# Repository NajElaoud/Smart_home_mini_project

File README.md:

# Smart_home_mini_project
Mini projet educatif

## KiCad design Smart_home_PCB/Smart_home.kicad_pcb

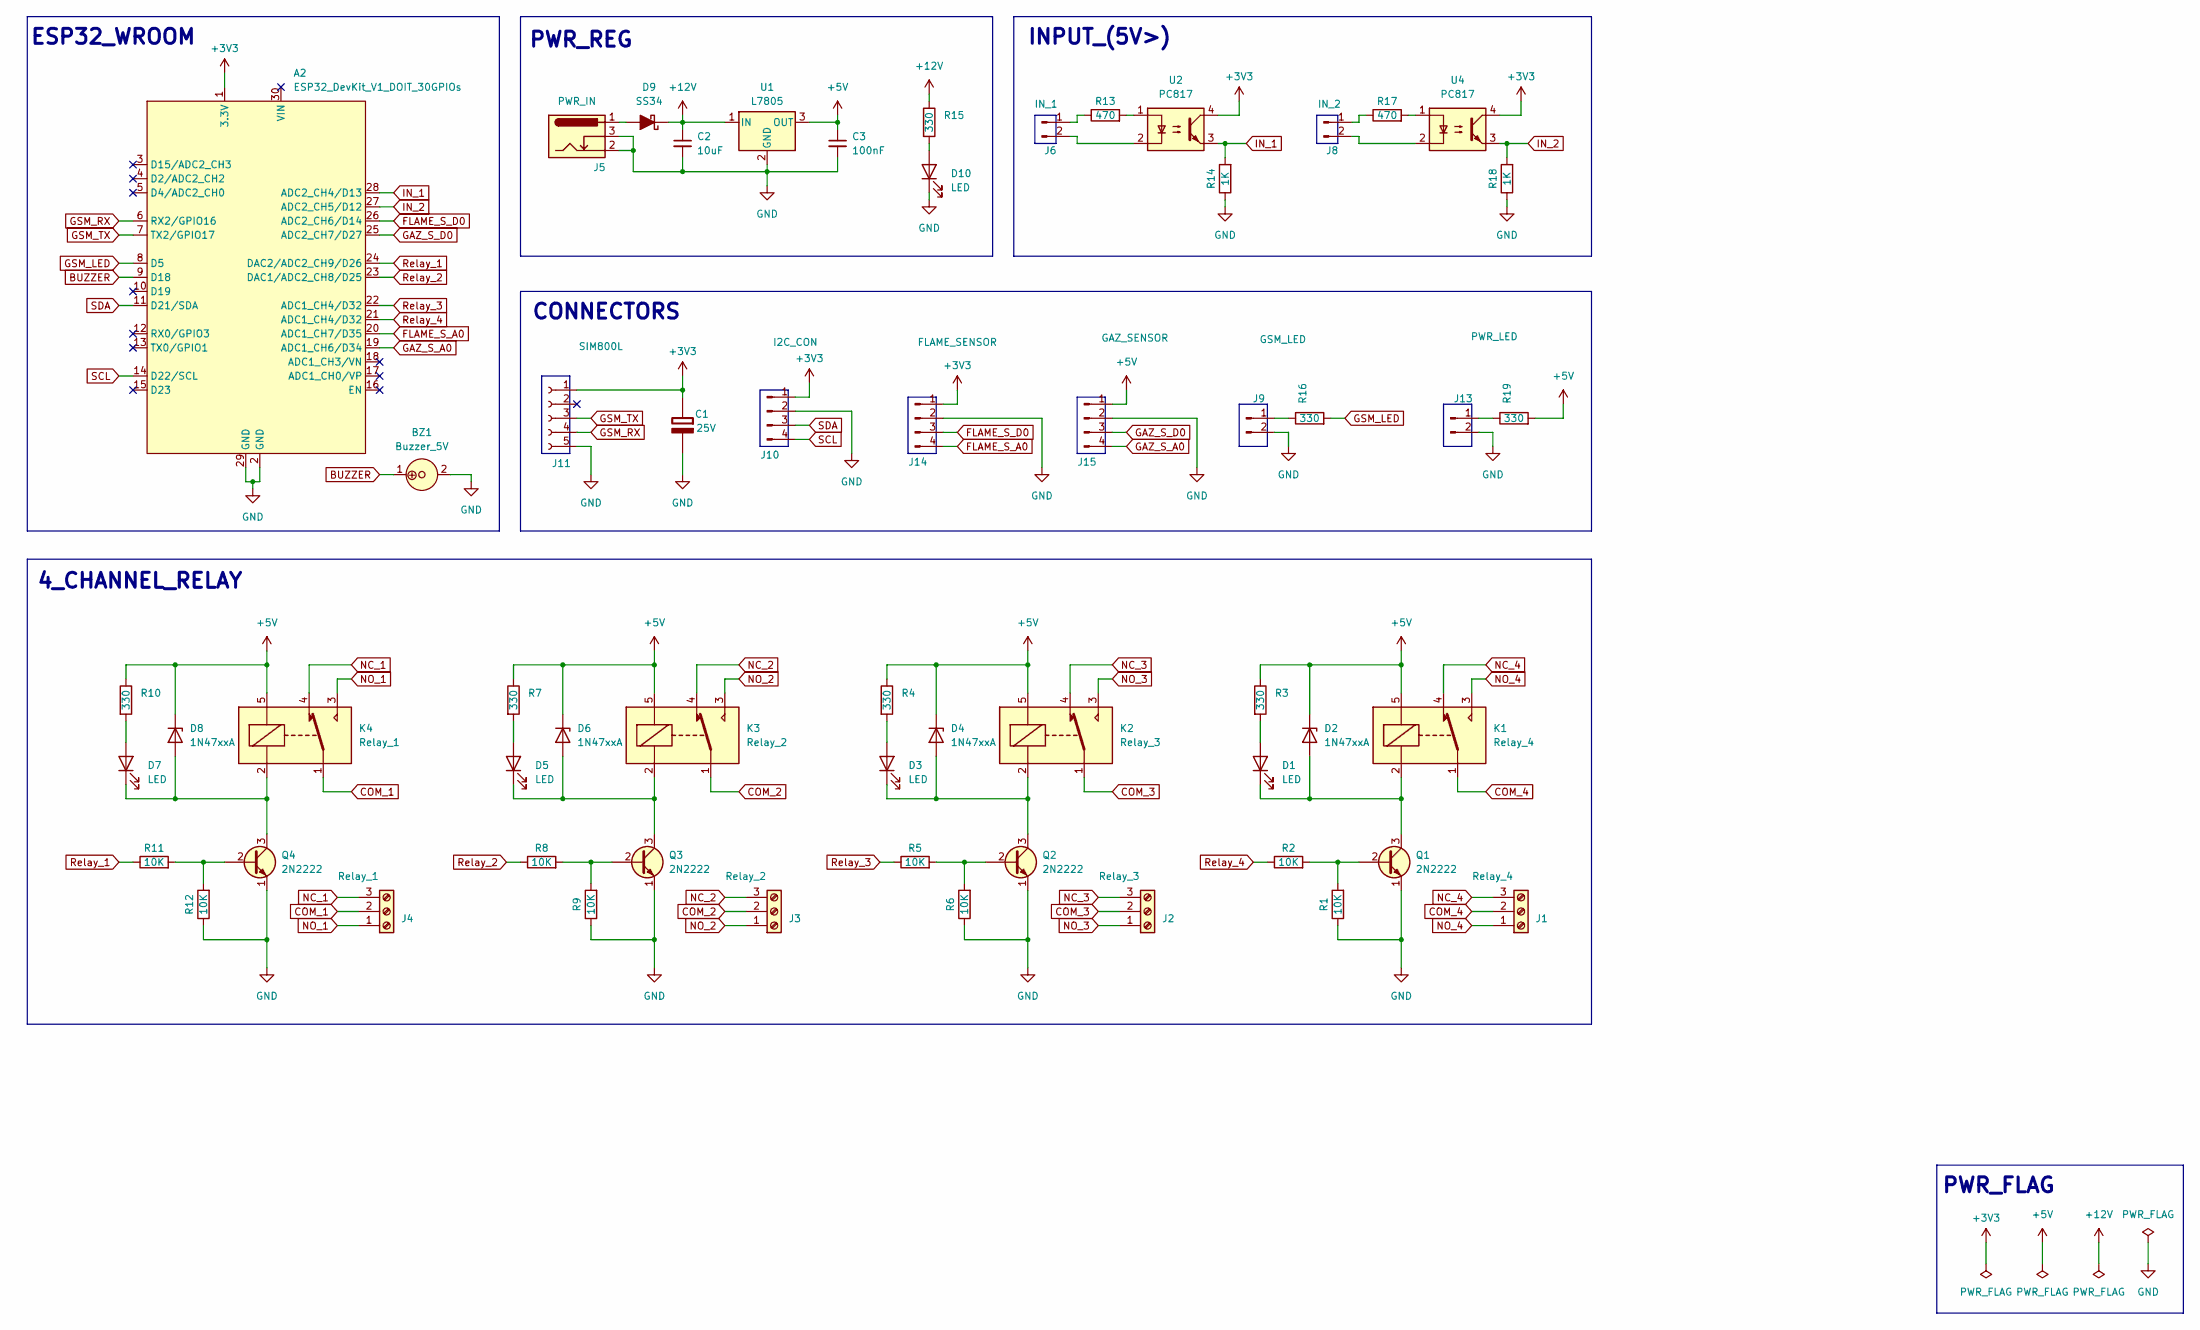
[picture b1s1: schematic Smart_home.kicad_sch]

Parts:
A2: ESP32_DevKit_V1_DOIT_30GPIOs; DOIT_ESP32_DEVKIT_30Pins
BZ1: Buzzer_5V; MagneticBuzzer_ProSignal_ABT-410-RC
C1: C-polar; CP_Radial_D6.3mm_P2.50mm; Rating 25V
C2: 10uF; C_Disc_D5.0mm_W2.5mm_P2.50mm
C3: 100nF; C_Disc_D5.0mm_W2.5mm_P2.50mm
D1, D3, D5, D7, D10: LED; LED_D3.0mm
D2, D4, D6, D8: 1N47xxA; D_T-1_P5.08mm_Horizontal
D9: SS34; D_DO-15_P2.54mm_Vertical_AnodeUp
J1: Relay_4; TerminalBlock_bornier-3_P5.08mm
J2: Relay_3; TerminalBlock_bornier-3_P5.08mm
J3: Relay_2; TerminalBlock_bornier-3_P5.08mm
J4: Relay_1; TerminalBlock_bornier-3_P5.08mm
J5: PWR_IN; BarrelJack_Wuerth_6941xx301002
J6: IN_1; TerminalBlock_bornier-2_P5.08mm
J8: IN_2; TerminalBlock_bornier-2_P5.08mm
J9: GSM_LED; Molex_KK-254_AE-6410-02A_1x02_P2.54mm_Vertical
J10: I2C_CON; JST_PH_B4B-PH-K_1x04_P2.00mm_Vertical
J11: SIM800L; PinHeader_1x05_P2.54mm_Vertical
J13: PWR_LED; Molex_KK-254_AE-6410-02A_1x02_P2.54mm_Vertical
J14: FLAME_SENSOR; JST_PH_B4B-PH-K_1x04_P2.00mm_Vertical
J15: GAZ_SENSOR; JST_PH_B4B-PH-K_1x04_P2.00mm_Vertical
K1: Relay_4; Relay_SPDT_SANYOU_SRD_Series_Form_C
K2: Relay_3; Relay_SPDT_SANYOU_SRD_Series_Form_C
K3: Relay_2; Relay_SPDT_SANYOU_SRD_Series_Form_C
K4: Relay_1; Relay_SPDT_SANYOU_SRD_Series_Form_C
Q1, Q2, Q3, Q4: 2N2222; TO-92
R1, R2, R5, R6, R8, R9, R11, R12: 10K; R_Axial_DIN0204_L3.6mm_D1.6mm_P5.08mm_Horizontal
R3, R4, R7, R10, R15, R16, R19: 330; R_Axial_DIN0204_L3.6mm_D1.6mm_P5.08mm_Horizontal
R13, R17: 470; R_Axial_DIN0204_L3.6mm_D1.6mm_P5.08mm_Horizontal
R14, R18: 1K; R_Axial_DIN0204_L3.6mm_D1.6mm_P5.08mm_Horizontal
U1: L7805; TO-220-3_Horizontal
U2, U4: PC817; DIP-4_W7.62mm

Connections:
+3V3: A2.1 (3.3V), C1.1 (+), J10.1, J11.1, J14.1, U2.4, U4.4
+5V: C3.1, D2.1 (K), D4.1 (K), D6.1 (K), D8.1 (K), J15.1, K1.5, K2.5, K3.5, K4.5, R3.1, R4.1, R7.1, R10.1, R19.2, U1.3 (OUT)
+12V: C2.1, D9.1 (K), R15.1, U1.1 (IN)
BUZZER: A2.9 (D18), BZ1.1
COM_1: J4.2, K4.1
COM_2: J3.2, K3.1
COM_3: J2.2, K2.1
COM_4: J1.2, K1.1
FLAME_S_A0: A2.20 (ADC1_CH7/D35), J14.4
FLAME_S_D0: A2.26 (ADC2_CH6/D14), J14.3
GAZ_S_A0: A2.19 (ADC1_CH6/D34), J15.4
GAZ_S_D0: A2.25 (ADC2_CH7/D27), J15.3
GND: A2.2 (GND), A2.29 (GND), BZ1.2, C1.2 (-), C2.2, C3.2, D10.1 (K), J5.2, J5.3, J9.2, J10.2, J11.5, J13.2, J14.2, J15.2, Q1.1 (E), Q2.1 (E), Q3.1 (E), Q4.1 (E), R1.1, R6.1, R9.1, R12.1, R14.1, R18.1, U1.2 (GND)
GSM_LED: A2.8 (D5), R16.2
GSM_RX: A2.6 (RX2/GPIO16), J11.4
GSM_TX: A2.7 (TX2/GPIO17), J11.3
IN_1: A2.28 (ADC2_CH4/D13), R14.2, U2.3
IN_2: A2.27 (ADC2_CH5/D12), R18.2, U4.3
NC_1: J4.3, K4.4
NC_2: J3.3, K3.4
NC_3: J2.3, K2.4
NC_4: J1.3, K1.4
NO_1: J4.1, K4.3
NO_2: J3.1, K3.3
NO_3: J2.1, K2.3
NO_4: J1.1, K1.3
unnamed: D1.2 (A), R3.2
unnamed: D1.1 (K), D2.2 (A), K1.2, Q1.3 (C)
unnamed: D3.2 (A), R4.2
unnamed: D3.1 (K), D4.2 (A), K2.2, Q2.3 (C)
unnamed: D5.2 (A), R7.2
unnamed: D5.1 (K), D6.2 (A), K3.2, Q3.3 (C)
unnamed: D7.2 (A), R10.2
unnamed: D7.1 (K), D8.2 (A), K4.2, Q4.3 (C)
unnamed: D9.2 (A), J5.1
unnamed: D10.2 (A), R15.2
unnamed: J6.1, R13.1
unnamed: J6.2, U2.2
unnamed: J8.1, R17.1
unnamed: J8.2, U4.2
unnamed: J9.1, R16.1
unnamed: J13.1, R19.1
unnamed: Q1.2 (B), R1.2, R2.2
unnamed: Q2.2 (B), R5.2, R6.2
unnamed: Q3.2 (B), R8.2, R9.2
unnamed: Q4.2 (B), R11.2, R12.2
unnamed: R13.2, U2.1
unnamed: R17.2, U4.1
Relay_1: A2.24 (DAC2/ADC2_CH9/D26), R11.1
Relay_2: A2.23 (DAC1/ADC2_CH8/D25), R8.1
Relay_3: A2.22 (ADC1_CH4/D32), R5.1
Relay_4: A2.21 (ADC1_CH4/D32), R2.1
SCL: A2.14 (D22/SCL), J10.4
SDA: A2.11 (D21/SDA), J10.3

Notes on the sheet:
PWR_REG
CONNECTORS
4_CHANNEL_RELAY
ESP32_WROOM
PWR_FLAG
INPUT_(5V>)

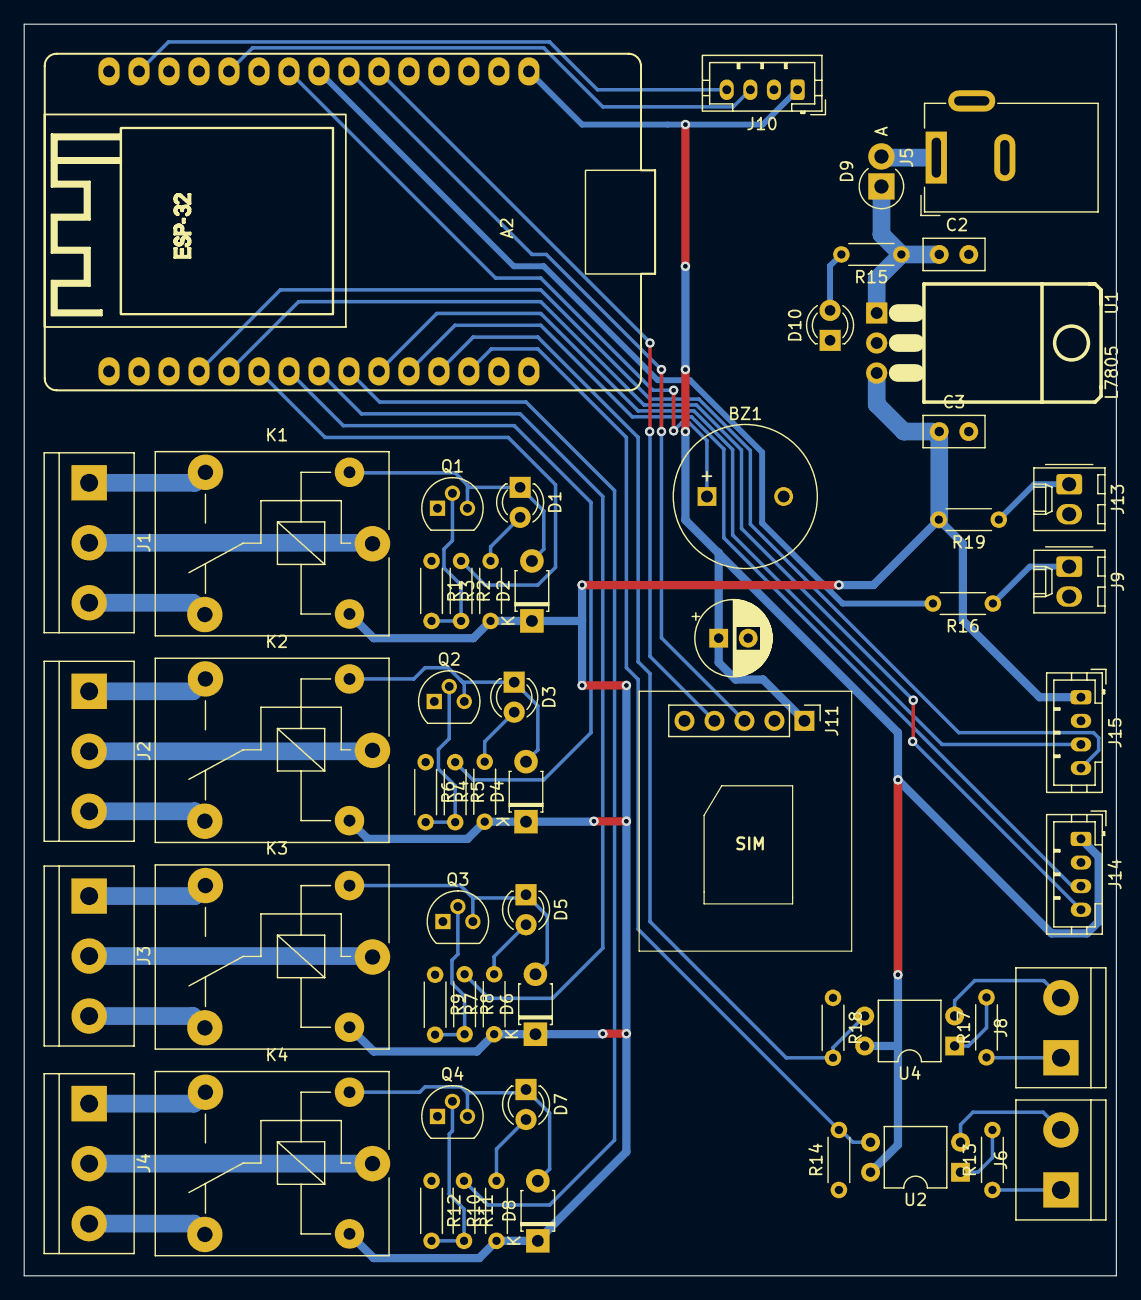
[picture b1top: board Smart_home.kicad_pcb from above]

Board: 2 copper layers, 92.5 x 106.0 mm, 58 parts (0 on the bottom side), 54 nets.

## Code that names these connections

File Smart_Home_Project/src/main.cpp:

//* Template ID (only if using Blynk.Cloud)
#define BLYNK_PRINT Serial
#define BLYNK_TEMPLATE_ID "TMPL2Fqpq1dXH"
#define BLYNK_TEMPLATE_NAME "smart home"
#define BLYNK_AUTH_TOKEN "eWVp4N7nibFjb5cihfrVReV-odIXRbQT"

//* Your WiFi credentials.
char ssid[] = "Galaxy A125533";
char pass[] = "11111111";

#include <Arduino.h>
#include <WiFi.h>
#include <WiFiClient.h>
#include <BlynkSimpleEsp32.h>
#include <Preferences.h>
// #include <SoftwareSerial.h>
#include <Wire.h>
#include <LiquidCrystal_I2C.h>

Preferences pref;

// SoftwareSerial SIM800L(6, 7); // RX | TX

//* Define the GPIO connected with Relays and Inputs
#define RelayPin1 26 // D26
#define RelayPin2 25 // D25
#define RelayPin3 32 // D32
#define RelayPin4 33 // D33

#define FLAME_S_D0 14 // D14
#define GAZ_S_D0 27   // D27
#define FLAME_S_A0 35 // D35
#define GAZ_S_A0 34   // D34
#define EXT_INPUT1 13 // D13
#define EXT_INPUT2 12 // D12

#define wifi_Led 2 // D2
#define GSM_Led 5  // D5
#define Buzzer 18  // D18

//* Virtual pins select
#define VPIN_BUTTON_1 V1 // vP1_ For relay n°1
#define VPIN_BUTTON_2 V2 // vP2_ For relay n°2
#define VPIN_BUTTON_3 V3 // vP3_ For relay n°3
#define VPIN_BUTTON_4 V4 // vP4_ For relay n°4
#define VPIN_BUTTON_C V5 // vP5_ For all relays OFF
#define VPIN_FLAME V6    // vP6_ For flame sensor input
#define VPIN_GAZ V7      // vP7_ For gas sensor inputq

//* Relay initial State
bool toggleState_1 = LOW; // Toggle state for relay 1
bool toggleState_2 = LOW; // Toggle state for relay 2
bool toggleState_3 = LOW; // Toggle state for relay 3
bool toggleState_4 = LOW; // Toggle state for relay 4

bool flame_state = false;
float gaz_value = 0.;
float gaz_value_disp = 0.;
int wifiFlag = 0;

//* State change
#define TURN_ON 1
#define TURN_OFF 0

char auth[] = BLYNK_AUTH_TOKEN;

BlynkTimer timer;

void all_SwitchOff();

//* When App button is pushed - switch the state
BLYNK_WRITE(VPIN_BUTTON_1)
{
  toggleState_1 = param.asInt();
  digitalWrite(RelayPin1, !toggleState_1);
  pref.putBool("Relay1", toggleState_1);
}

BLYNK_WRITE(VPIN_BUTTON_2)
{
  toggleState_2 = param.asInt();
  digitalWrite(RelayPin2, !toggleState_2);
  pref.putBool("Relay2", toggleState_2);
}

BLYNK_WRITE(VPIN_BUTTON_3)
{
  toggleState_3 = param.asInt();
  digitalWrite(RelayPin3, !toggleState_3);
  pref.putBool("Relay3", toggleState_3);
}

BLYNK_WRITE(VPIN_BUTTON_4)
{
  toggleState_4 = param.asInt();
  digitalWrite(RelayPin4, !toggleState_4);
  pref.putBool("Relay4", toggleState_4);
}

BLYNK_WRITE(VPIN_BUTTON_C)
{
  all_SwitchOff();
}

void checkBlynkStatus()
{ // called every 3 seconds by SimpleTimer
  bool isconnected = Blynk.connected();
  if (isconnected == false)
  {
    wifiFlag = 1;
    digitalWrite(wifi_Led, LOW);
    Serial.println("Blynk Not Connected");
  }
  if (isconnected == true)
  {
    wifiFlag = 0;
    digitalWrite(wifi_Led, HIGH);
    Serial.println("Blynk Connected");
  }
}

BLYNK_CONNECTED()
{
  // update the latest state to the server
  Blynk.virtualWrite(VPIN_BUTTON_1, toggleState_1);
  Blynk.virtualWrite(VPIN_BUTTON_2, toggleState_2);
  Blynk.virtualWrite(VPIN_BUTTON_3, toggleState_3);
  Blynk.virtualWrite(VPIN_BUTTON_4, toggleState_4);

  Blynk.syncVirtual(VPIN_FLAME);
  Blynk.syncVirtual(VPIN_GAZ);
}

void readSensor()
{
  int flame = digitalRead(FLAME_S_D0);
  if (isnan(flame))
  {
    Serial.println("Failed to read data from FLAME sensor!");
    return;
  }
  else
  {
    flame_state = flame;
    if (flame == 1)
    {
      Serial.printf("!! FLAME Detected!!\n");
    }
  }

  int gaz = analogRead(GAZ_S_A0);
  gaz_value_disp = map(gaz, 0, 1023, 0, 100);
  if (isnan(gaz))
  {
    Serial.println("Failed to read data from MQ2 sensor!");
    return;
  }
  else
  {
    gaz_value = gaz;
    Serial.printf("MQ2 sensor value: %.2f\n", gaz_value);
  }
}

void sendSensorData()
{
  readSensor();
  //* GAS_SENSOR
  Blynk.virtualWrite(VPIN_FLAME, flame_state);
  if (gaz_value > 700)
  {
    Blynk.logEvent("Warning! Gas leak detected");
    digitalWrite(RelayPin2, TURN_ON);
    digitalWrite(Buzzer, HIGH);
  }
  Blynk.virtualWrite(VPIN_GAZ, gaz_value_disp);

  //* FLAME_SENSOR
  if (flame_state == HIGH)
  {
    digitalWrite(Buzzer, LOW);
  }
  else if (flame_state == LOW)
  {
    Blynk.logEvent("Warning! Fire was detected");
    digitalWrite(Buzzer, HIGH);
  }
  Blynk.virtualWrite(VPIN_FLAME, flame_state);
}

void all_SwitchOff()
{
  //? Relay_1
  toggleState_1 = 0;
  digitalWrite(RelayPin1, HIGH);
  pref.putBool("Relay1", toggleState_1);
  Blynk.virtualWrite(VPIN_BUTTON_1, toggleState_1);
  delay(100);
  //? Relay_2
  toggleState_2 = 0;
  digitalWrite(RelayPin2, HIGH);
  pref.putBool("Relay2", toggleState_2);
  Blynk.virtualWrite(VPIN_BUTTON_2, toggleState_2);
  delay(100);
  //? Relay_3
  toggleState_3 = 0;
  digitalWrite(RelayPin3, HIGH);
  pref.putBool("Relay3", toggleState_3);
  Blynk.virtualWrite(VPIN_BUTTON_3, toggleState_3);
  delay(100);
  //? Relay_4
  toggleState_4 = 0;
  digitalWrite(RelayPin4, HIGH);
  pref.putBool("Relay4", toggleState_4);
  Blynk.virtualWrite(VPIN_BUTTON_4, toggleState_4);
  delay(100);
  //? Sensor input
  Blynk.virtualWrite(VPIN_FLAME, flame_state);
  Blynk.virtualWrite(VPIN_GAZ, gaz_value);
}

void getRelayState()
{
  Serial.println("reading data from NVS");

  toggleState_1 = pref.getBool("Relay1", TURN_OFF);
  digitalWrite(RelayPin1, !toggleState_1);
  Blynk.virtualWrite(VPIN_BUTTON_1, toggleState_1);
  delay(200);

  toggleState_2 = pref.getBool("Relay2", TURN_OFF);
  digitalWrite(RelayPin2, !toggleState_2);
  Blynk.virtualWrite(VPIN_BUTTON_2, toggleState_2);
  delay(200);

  toggleState_3 = pref.getBool("Relay3", TURN_OFF);
  digitalWrite(RelayPin3, !toggleState_3);
  Blynk.virtualWrite(VPIN_BUTTON_3, toggleState_3);
  delay(200);

  toggleState_4 = pref.getBool("Relay4", TURN_OFF);
  digitalWrite(RelayPin4, !toggleState_4);
  Blynk.virtualWrite(VPIN_BUTTON_4, toggleState_4);
  delay(200);
}

void setup()
{
  Serial.begin(9600);
  // SIM800L.begin(9600);
  //  Open namespace in read-write mode
  pref.begin("Relay_State", false);

  pinMode(RelayPin1, OUTPUT);
  pinMode(RelayPin2, OUTPUT);
  pinMode(RelayPin3, OUTPUT);
  pinMode(RelayPin4, OUTPUT);

  pinMode(wifi_Led, OUTPUT);

  // During Starting all Relays should TURN OFF
  digitalWrite(RelayPin1, !toggleState_1);
  digitalWrite(RelayPin2, !toggleState_2);
  digitalWrite(RelayPin3, !toggleState_3);
  digitalWrite(RelayPin4, !toggleState_4);

  digitalWrite(wifi_Led, LOW);

  WiFi.begin(ssid, pass);
  timer.setInterval(2000L, checkBlynkStatus); // check if Blynk server is connected every 2 seconds
  timer.setInterval(1000L, sendSensorData);   // Sending Sensor Data to Blynk Cloud every 1 second
  Blynk.config(auth);
  delay(1000);

  getRelayState(); // fetch data from NVS Flash Memory
  //  delay(1000);
}

void loop()
{
  Blynk.run();
  timer.run(); // Initiates SimpleTimer
}

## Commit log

2024-04-25 Project Initial code_NO_addONS
2024-04-25 Project PCB_Design
